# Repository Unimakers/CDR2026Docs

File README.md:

---
title: "README & MICRODOC"
layout: default
---
# Documentation de l'association UniMakers pour la CDR2026

Table de contenu:
- [Documentation de l'association UniMakers pour la CDR2026](#documentation-de-lassociation-unimakers-pour-la-cdr2026)
  - [Comment créer une page ?](#comment-créer-une-page-)
  - [Comment afficher un modèle 3D](#comment-afficher-un-modèle-3d)

## Comment créer une page ?

Allez dans le dossier correspondant au thème de la page, 

exemple pour l'élec du robot principal: Robot/Elec/

Créez un nouveau fichier pour votre nouvelle page.

Rajoutez en haut du fichier:

```yaml
---
title: "Titre de votre page"
layout: technical
---
```

Utilisez `layout: technical` si vous souhaitez utiliser les modèles 3D ou le visualiseur kicad dans votre page, sinon utilisez `layout: default` pour réduire le temps de chargement de la page en supprimant les imports inutiles.

Les clés de définition doivent se trouver entre les deux `---`.
Après le deuxième `---` vous pouvez écrire le contenu de la page **en markdown**.

Vous pouvez rajouter un 
```yaml
has_children: true
```
si vous souhaitez faire de cette page une page de catégorie qui aura donc des sous-pages.

Pour mettre cette page en tant que sous-page dans une catégorie (et non à la racine) vous devez rajouter une clé `parent` et eventuellement une clé `grand_parent`:

La clé `parent` permettra de définir le parent direct de la page, la valeur doit etre le titre de la page parent.

Exemple, si vous créez une page dans la catégorie `Electronique` du `Robot` vous devrez définir la clé `parent` avec la valeur `Electronique`.

La clé `grand_parent` permettra de définir le grand parent de la page, c'est à dire la catégorie racine, la valeur doit etre le titre du grand parent.

Exemple, si vous créez une page dans la catégorie `Electronique` du `Robot` vous devrez définir la clé `grand_parent` avec la valeur `Robot`

Actuellement l'arbre des titres et catégories est:
```
Racine:
|-Présentation
|-Robot:
| |-Mécanique
| |-Stratégie
|-Pami:
| |-Mécanique
| |-Stratégie
|-Electronique
|-Programmation
| |-Déplacement
| |-Détection
```

Exemple pour créer une catégorie `Actionneurs` dans `Mécanique` sous `Robot` et ensuite créer une page `Pince`:

On crée le dossier `Robot/Meca/Actionneurs` (c'est mieux pour la lisibilité de trier les pages dans des dossiers, techniquement on pourrait tout laisser à la racine).

On crée le fichier `Robot/Meca/Actionneurs/Actionneurs.md`:
```md
---
title: Actionneurs
parent: Mécanique
grand_parent: Robot
has_children: true
layout: default
---
# Les actionneurs de notre robot
Le robot a besoin d'actionneurs pour fonctionner
```

On crée le fichier `Robot/Meca/Actionneurs/Pince.md`:
```md
---
title: Pince
parent: Actionneurs
grand_parent: Mécanique
has_children: true
layout: default
---
# La pince du robot
La pince du robot, nécessaire pour attraper.....
```

## Comment afficher un modèle 3D

Assurez vous d'avoir défini `layout: technical` au lieu de `layout: default`.

Dans votre code markdown rajoutez:
```md
<model-viewer alt="Texte de déscription du modèle 3D" src="url / chemin du modèle 3D" ar shadow-intensity="1" camera-controls touch-action="pan-y"></model-viewer>

Ou

{%raw%}{{%include model3D.html alt="Texte de description du modèle 3D" model="url / chemin du modèle 3D"%}}{%endraw%}
``` 
Le modèle 3D **doit** être en format GLTF / GLB.

## Comment utiliser le visionneur KiCad

Assurez vous d'avoir défini `layout: technical` au lieu de `layout: default`.

- Si vous ne souhaitez que le schématique:

Dans votre code markdown rajoutez:
```md
<kicanvas-embed src="chemin/vers/fichier.kicad_sch" controls="basic"></kicanvas-embed>
```

- Si vous souhaitez le schématique ET la PCB;

Dans votre code markdown rajoutez:
```md
<kicanvas-embed controls="full">
<kicanvas-source src="chemin/vers/fichier.kicad_sch"></kicanvas-source>
<kicanvas-source src="chemin/vers/fichier.kicad_pcb"></kicanvas-source>
</kicanvas-embed>
```

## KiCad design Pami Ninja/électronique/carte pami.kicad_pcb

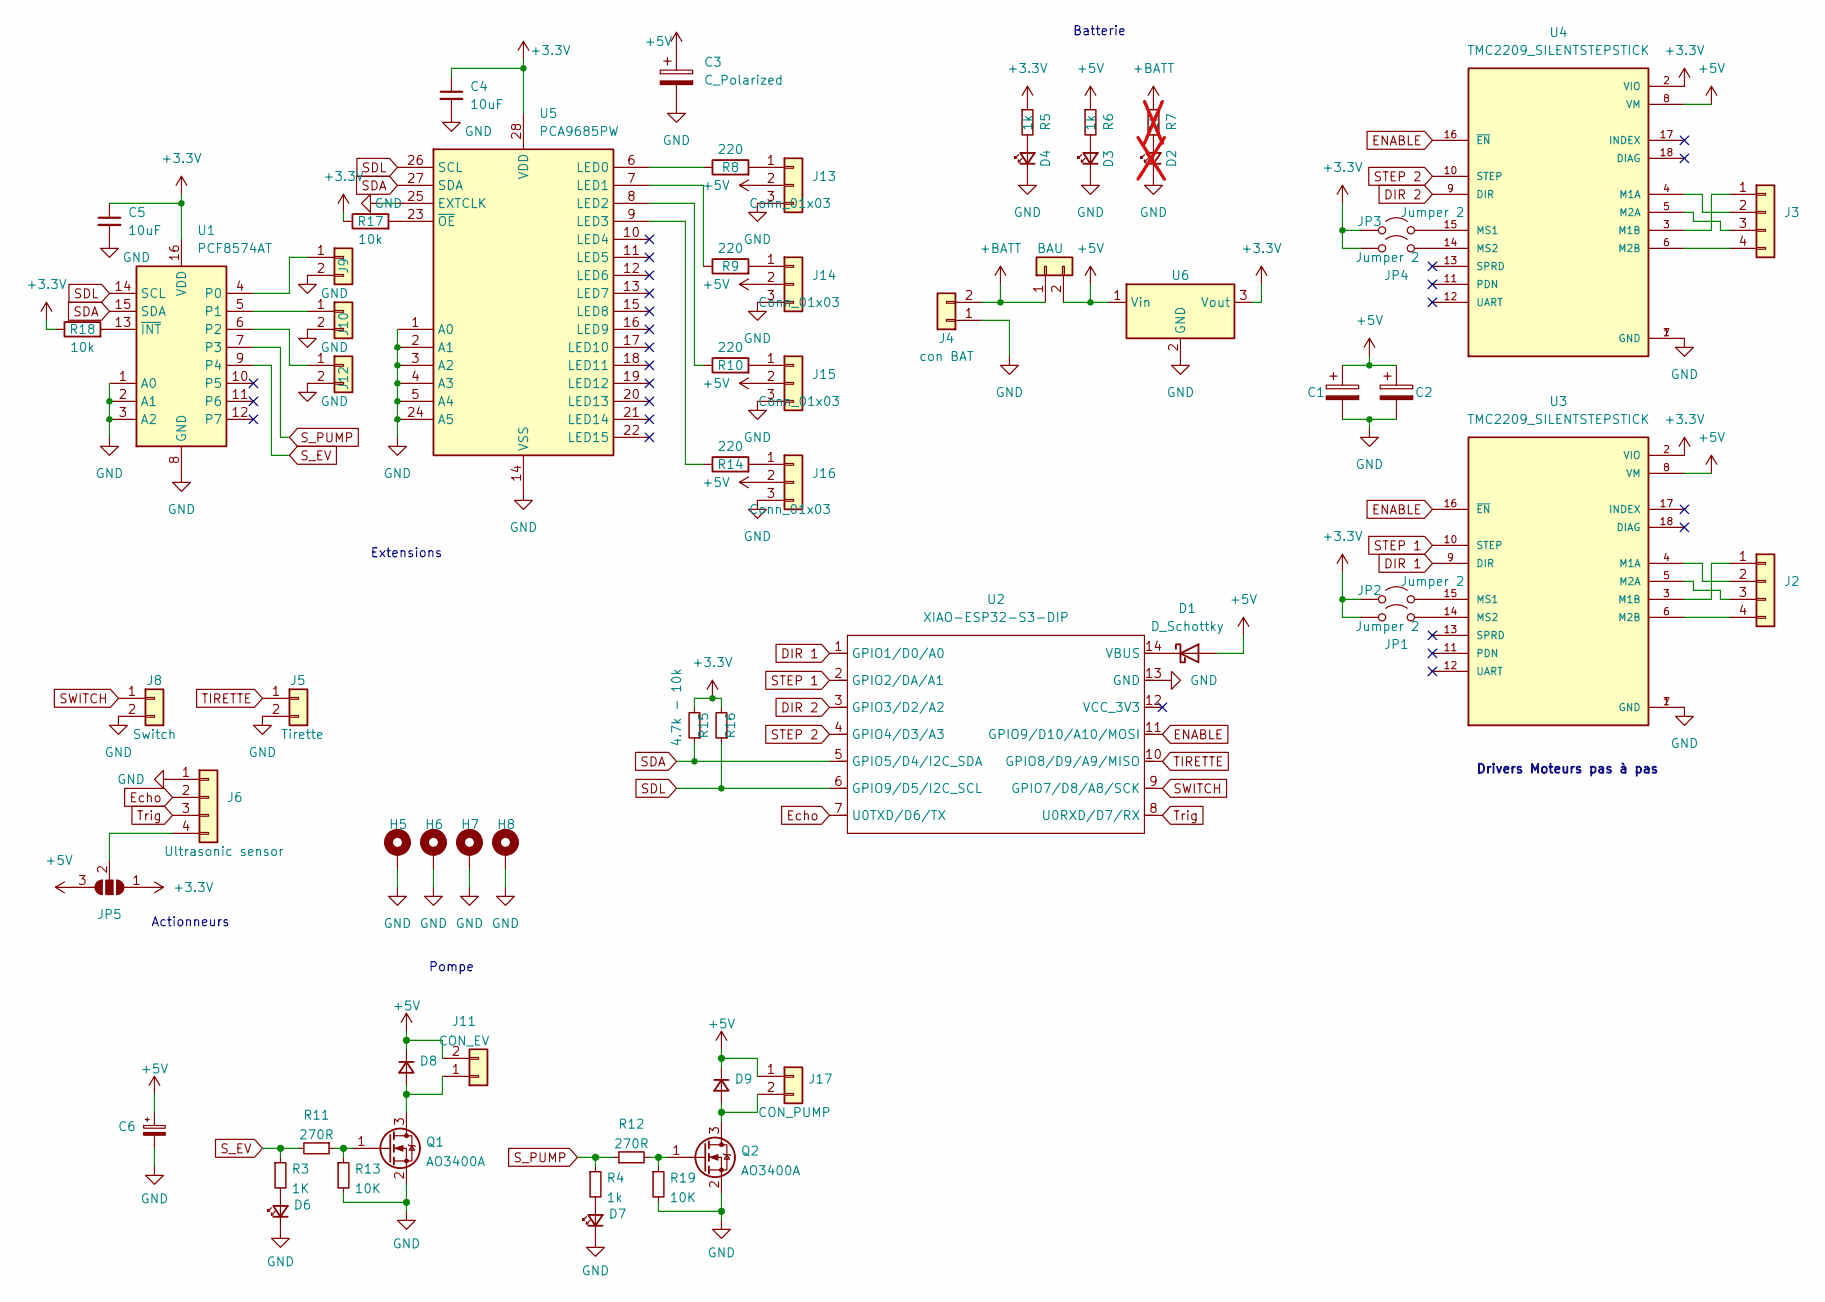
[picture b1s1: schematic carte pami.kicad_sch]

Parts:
C1, C2: C_Polarized; CP_Radial_D8.0mm_P3.80mm
C3: C_Polarized; CP_Radial_D8.0mm_P5.00mm
C4, C5: 10uF; C_1206_3216Metric_Pad1.33x1.80mm_HandSolder
C6: C_Polarized_Small; CP_Radial_D8.0mm_P5.00mm
D1: D_Schottky; D_DO-41_SOD81_P10.16mm_Horizontal
D2: LED_Small; LED_1206_3216Metric_Pad1.42x1.75mm_HandSolder; not fitted
D3, D4, D6, D7: LED_Small; LED_1206_3216Metric_Pad1.42x1.75mm_HandSolder
D8, D9: D_Small; D_SMA_Handsoldering
H5, H6, H7, H8: MountingHole_3.2mm_M3_Pad
J1: BAU; Molex_KK-254_AE-6410-02A_1x02_P2.54mm_Vertical
J2, J3: Conn_01x04; Molex_KK-254_AE-6410-04A_1x04_P2.54mm_Vertical
J4: con BAT; AMASS_XT60-F_1x02_P7.20mm_Vertical
J5: Tirette; Molex_KK-254_AE-6410-02A_1x02_P2.54mm_Vertical
J6: Ultrasonic sensor; Molex_KK-254_AE-6410-04A_1x04_P2.54mm_Vertical
J8: Switch; Molex_KK-254_AE-6410-02A_1x02_P2.54mm_Vertical
J9, J10, J12: Conn_01x02; Molex_KK-254_AE-6410-02A_1x02_P2.54mm_Vertical
J11: CON_EV; Molex_KK-254_AE-6410-02A_1x02_P2.54mm_Vertical
J13, J14, J15, J16: Conn_01x03; PinHeader_1x03_P2.54mm_Vertical
J17: CON_PUMP; Molex_KK-254_AE-6410-02A_1x02_P2.54mm_Vertical
JP1, JP2, JP3, JP4: Jumper 2; SolderJumper-2_P1.3mm_Open_RoundedPad1.0x1.5mm
JP5: SolderJumper_3_Open; SolderJumper-3_P1.3mm_Open_RoundedPad1.0x1.5mm_NumberLabels
Q1, Q2: AO3400A; SOT-23
R3: 1K; R_1206_3216Metric_Pad1.30x1.75mm_HandSolder
R4, R5, R6: 1k; R_1206_3216Metric_Pad1.30x1.75mm_HandSolder
R7: 1k; R_1206_3216Metric_Pad1.30x1.75mm_HandSolder; not fitted
R8, R9, R10, R14: 220; R_1206_3216Metric_Pad1.30x1.75mm_HandSolder
R11, R12: 270R; R_1206_3216Metric_Pad1.30x1.75mm_HandSolder
R13, R19: 10K; R_1206_3216Metric_Pad1.30x1.75mm_HandSolder
R15: 4.7k - 10k; R_1206_3216Metric_Pad1.30x1.75mm_HandSolder
R16: R_Small; R_1206_3216Metric_Pad1.30x1.75mm_HandSolder
R17, R18: 10k; R_1206_3216Metric_Pad1.30x1.75mm_HandSolder
U1: PCF8574AT; SOIC-16W_7.5x10.3mm_P1.27mm
U2: XIAO-ESP32-S3-DIP; XIAO-ESP32S3-DIP
U3, U4: TMC2209_SILENTSTEPSTICK; MODULE_TMC2209_SILENTSTEPSTICK; PARTREV 1.20
U5: PCA9685PW; TSSOP-28_4.4x9.7mm_P0.65mm
U6: TSR1-2433E; Converter_DCDC_TRACO_TSR1-xxxxE_THT

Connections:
+3.3V: C4.1, C5.1, JP1.1 (A), JP2.1 (A), JP3.1 (A), JP4.1 (A), JP5.1 (A), R5.1, R15.2, R16.2, R17.1, R18.1, U1.16 (VDD), U3.2 (VIO), U4.2 (VIO), U5.28 (VDD), U6.3 (Vout)
+5V: C1.1, C2.1, C3.1, C6.1, D1.2 (A), D8.1 (K), D9.1 (K), J1.2, J11.2, J13.2, J14.2, J15.2, J16.2, J17.1, JP5.3 (B), R6.1, U3.8 (VM), U4.8 (VM), U6.1 (Vin)
+BATT: J1.1, J4.2, R7.1
DIR 1: U2.1 (GPIO1/D0/A0), U3.9 (DIR)
DIR 2: U2.3 (GPIO3/D2/A2), U4.9 (DIR)
ENABLE: U2.11 (GPIO9/D10/A10/MOSI), U3.16 (~EN), U4.16 (~EN)
Echo: J6.2, U2.7 (U0TXD/D6/TX)
GND: C1.2, C2.2, C3.2, C4.2, C5.2, C6.2, D2.1 (K), D3.1 (K), D4.1 (K), D6.1 (K), D7.1 (K), H5.1, H6.1, H7.1, H8.1, J4.1, J5.2, J6.1, J8.2, J9.2, J10.2, J12.2, J13.3, J14.3, J15.3, J16.3, Q1.2 (S), Q2.2 (S), R13.2, R19.2, U1.1 (A0), U1.2 (A1), U1.3 (A2), U1.8 (GND), U2.13 (GND), U3.1 (GND), U3.7 (GND), U4.1 (GND), U4.7 (GND), U5.1 (A0), U5.2 (A1), U5.3 (A2), U5.4 (A3), U5.5 (A4), U5.14 (VSS), U5.24 (A5), U5.25 (EXTCLK), U6.2 (GND)
unnamed: D1.1 (K), U2.14 (VBUS)
unnamed: D2.2 (A), R7.2
unnamed: D3.2 (A), R6.2
unnamed: D4.2 (A), R5.2
unnamed: D6.2 (A), R3.2
unnamed: D7.2 (A), R4.2
unnamed: D8.2 (A), J11.1, Q1.3 (D)
unnamed: D9.2 (A), J17.2, Q2.3 (D)
unnamed: J2.1, U3.3 (M1B)
unnamed: J2.2, U3.4 (M1A)
unnamed: J2.3, U3.5 (M2A)
unnamed: J2.4, U3.6 (M2B)
unnamed: J3.1, U4.3 (M1B)
unnamed: J3.2, U4.4 (M1A)
unnamed: J3.3, U4.5 (M2A)
unnamed: J3.4, U4.6 (M2B)
unnamed: J6.4, JP5.2 (C)
unnamed: J9.1, U1.4 (P0)
unnamed: J10.1, U1.5 (P1)
unnamed: J12.1, U1.6 (P2)
unnamed: J13.1, R8.2
unnamed: J14.1, R9.2
unnamed: J15.1, R10.2
unnamed: J16.1, R14.2
unnamed: JP1.2 (B), U3.14 (MS2)
unnamed: JP2.2 (B), U3.15 (MS1)
unnamed: JP3.2 (B), U4.15 (MS1)
unnamed: JP4.2 (B), U4.14 (MS2)
unnamed: Q1.1 (G), R11.1, R13.1
unnamed: Q2.1 (G), R12.2, R19.1
unnamed: R18.2, U1.13 (~INT)
unnamed: R8.1, U5.6 (LED0)
unnamed: R9.1, U5.7 (LED1)
unnamed: R10.1, U5.8 (LED2)
unnamed: R14.1, U5.9 (LED3)
unnamed: R17.2, U5.23 (~OE)
SDA: R15.1, U1.15 (SDA), U2.5 (GPIO5/D4/I2C_SDA), U5.27 (SDA)
SDL: R16.1, U1.14 (SCL), U2.6 (GPIO9/D5/I2C_SCL), U5.26 (SCL)
STEP 1: U2.2 (GPIO2/DA/A1), U3.10 (STEP)
STEP 2: U2.4 (GPIO4/D3/A3), U4.10 (STEP)
SWITCH: J8.1, U2.9 (GPIO7/D8/A8/SCK)
S_EV: R3.1, R11.2, U1.9 (P4)
S_PUMP: R4.1, R12.1, U1.7 (P3)
TIRETTE: J5.1, U2.10 (GPIO8/D9/A9/MISO)
Trig: J6.3, U2.8 (U0RXD/D7/RX)

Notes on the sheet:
Batterie
Pompe
Actionneurs
Drivers Moteurs pas à pas
Extensions

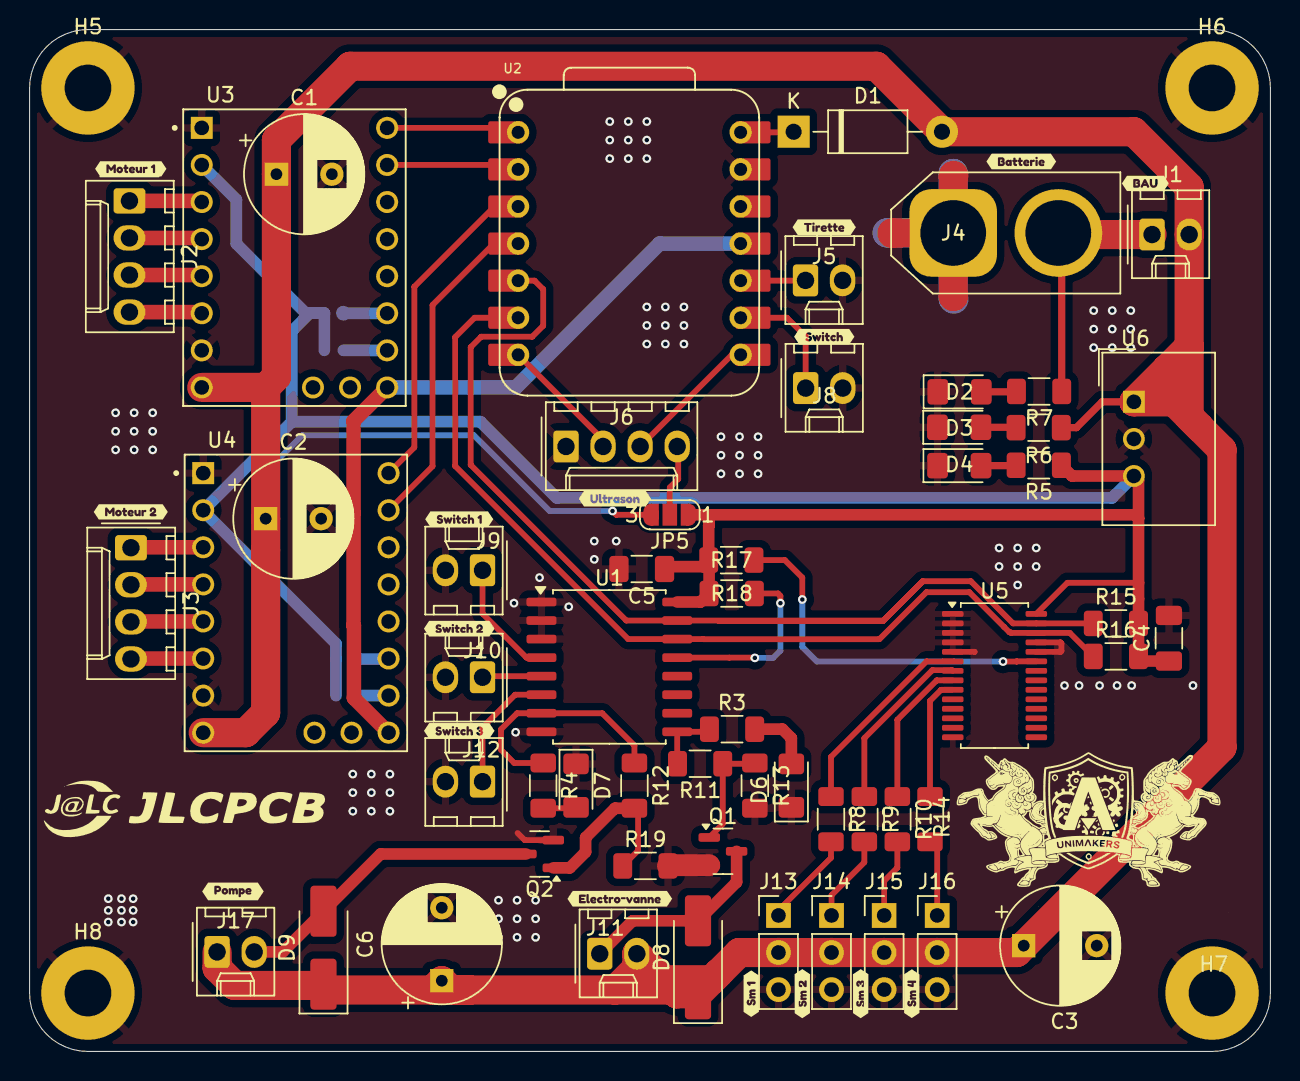
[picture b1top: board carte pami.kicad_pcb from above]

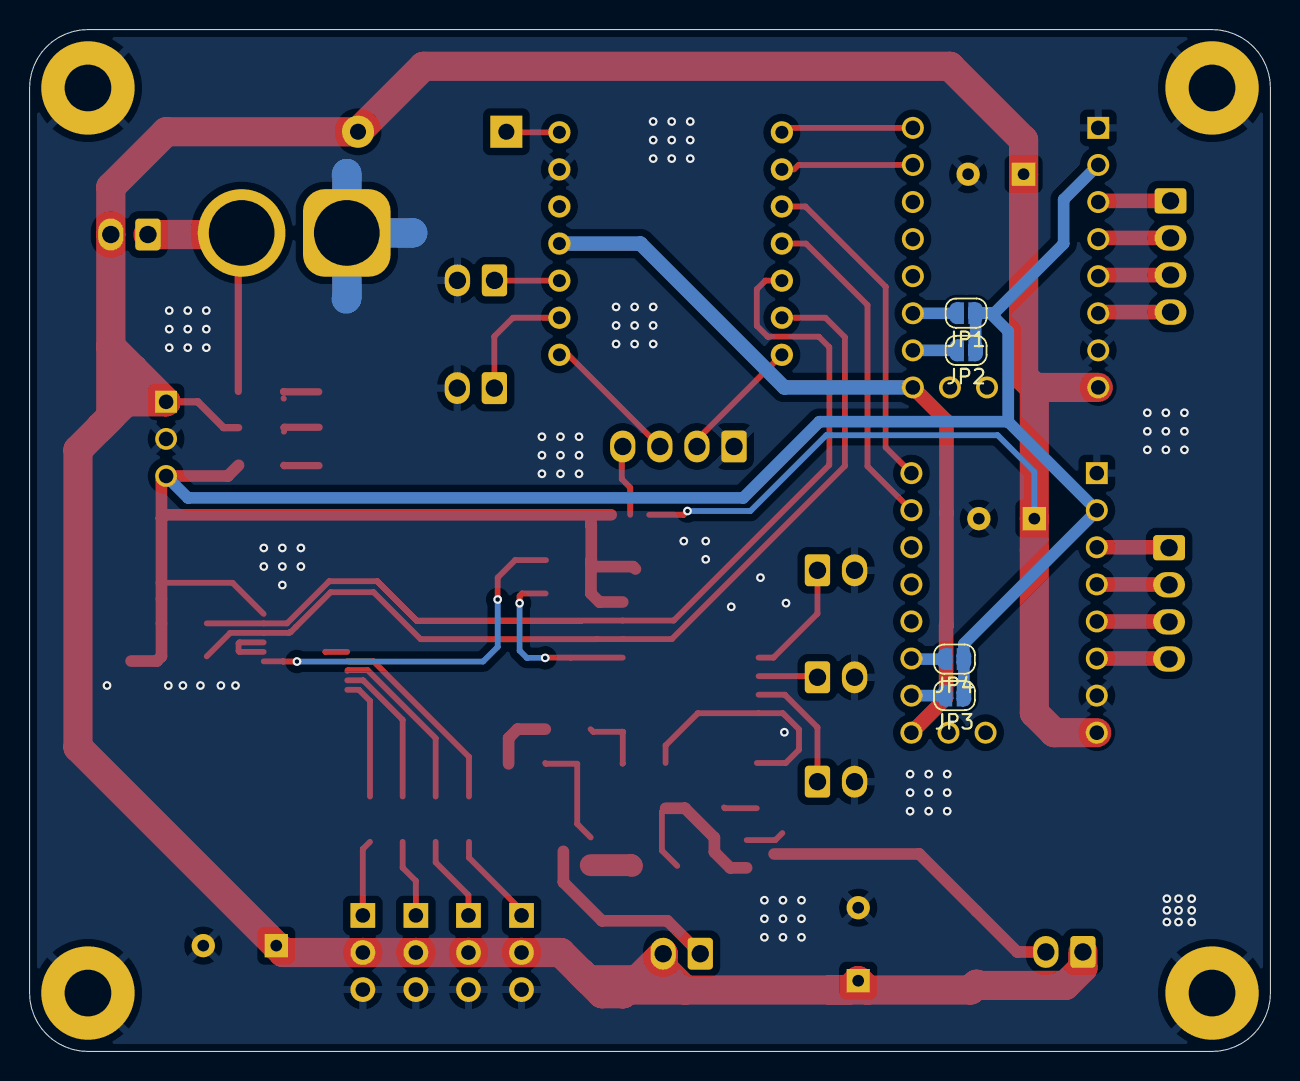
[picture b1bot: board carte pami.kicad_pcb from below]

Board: 2 copper layers, 85.0 x 70.0 mm, 80 parts (4 on the bottom side), 53 nets.

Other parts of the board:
kibuzzard-69BD4C51: G***; kibuzzard-69BD4C51
kibuzzard-69BD4C98: G***; kibuzzard-69BD4C98
kibuzzard-69BD4CAE: G***; kibuzzard-69BD4CAE
kibuzzard-69BD4CC4: G***; kibuzzard-69BD4CC4
kibuzzard-69BD4CEF: G***; kibuzzard-69BD4CEF
kibuzzard-69BD4D3C: G***; kibuzzard-69BD4D3C
kibuzzard-69BD4D5C: G***; kibuzzard-69BD4D5C
kibuzzard-69BD4D83: G***; kibuzzard-69BD4D83
kibuzzard-69BD4D93: G***; kibuzzard-69BD4D93
kibuzzard-69BD4EA4: G***; kibuzzard-69BD4EA4
kibuzzard-69BD4EB4: G***; kibuzzard-69BD4EB4
kibuzzard-69BD4EFE: G***; kibuzzard-69BD4EFE
kibuzzard-69BD4FA7: G***; kibuzzard-69BD4FA7
kibuzzard-69BD4FC7: G***; kibuzzard-69BD4FC7
kibuzzard-69BD4FD6: G***; kibuzzard-69BD4FD6
kibuzzard-69BD4FE1: G***; kibuzzard-69BD4FE1

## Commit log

2025-11-28 init of CDR2026 Docs
2025-11-28 some changes
2026-01-01 Bump just-the-docs from 0.10.1 to 0.10.2
    Bumps [just-the-docs](https://github.com/just-the-docs/just-the-docs) from 0.10.1 to 0.10.2.
    - [Release notes](https://github.com/just-the-docs/just-the-docs/releases)
    - [Changelog](https://github.com/just-the-docs/just-the-docs/blob/main/CHANGELOG.md)
    - [Commits](https://github.com/just-the-docs/just-the-docs/compare/v0.10.1...v0.10.2)
    ---
    updated-dependencies:
2026-01-02 Bump just-the-docs from 0.10.1 to 0.11.0
    Bumps [just-the-docs](https://github.com/just-the-docs/just-the-docs) from 0.10.1 to 0.11.0.
    - [Release notes](https://github.com/just-the-docs/just-the-docs/releases)
    - [Changelog](https://github.com/just-the-docs/just-the-docs/blob/main/CHANGELOG.md)
    - [Commits](https://github.com/just-the-docs/just-the-docs/compare/v0.10.1...v0.11.0)
    ---
    updated-dependencies:
2026-01-16 first commit doc elec
2026-01-19 intro
2026-01-20 test model 3d
2026-01-20 add kicanvas
2026-01-20 test 2
2026-01-20 test pcb
2026-01-20 add lfs
2026-01-20 partie 2
2026-01-20 remove lfs
2026-01-20 Bump just-the-docs from 0.10.1 to 0.11.1
    Bumps [just-the-docs](https://github.com/just-the-docs/just-the-docs) from 0.10.1 to 0.11.1.
    - [Release notes](https://github.com/just-the-docs/just-the-docs/releases)
    - [Changelog](https://github.com/just-the-docs/just-the-docs/blob/main/CHANGELOG.md)
    - [Commits](https://github.com/just-the-docs/just-the-docs/compare/v0.10.1...v0.11.1)
    ---
    updated-dependencies:
2026-01-20 script url
2026-01-20 Disable LFS in GitHub Pages workflow
2026-01-20 Update GitHub Actions workflow for LFS support
    Added steps to handle Git LFS authentication and checkout.
2026-01-20 avancée partie elec
2026-01-21 avancement
2026-01-21 création pami ninja
2026-01-21 sous page pami ninja
2026-01-21 actionneurs base roulante ficher créer
2026-01-21 avancée conception
2026-01-21 base roulante pami ninja
2026-01-21 début edit de la presentation de la coupe
2026-01-25 test + fix
2026-01-25 on teste
2026-01-26 test réglage problème navigation
2026-01-26 aaaaa
2026-01-26 test modif navig
2026-01-26 changement nav order
2026-01-26 aaaaaaaaaaaaaaaaaaaaaaaaaa
2026-01-26 pami ninja validation.md
2026-01-26 pami ninja
2026-01-26 pami
2026-01-26 pami supprimé
2026-01-26 modif
2026-01-26 test
2026-01-26 on test encore
2026-01-26 azdhaefhfaeo
2026-01-26 ajoiausbha
2026-01-26 Bump just-the-docs from 0.10.1 to 0.12.0
    Bumps [just-the-docs](https://github.com/just-the-docs/just-the-docs) from 0.10.1 to 0.12.0.
    - [Release notes](https://github.com/just-the-docs/just-the-docs/releases)
    - [Changelog](https://github.com/just-the-docs/just-the-docs/blob/main/CHANGELOG.md)
    - [Commits](https://github.com/just-the-docs/just-the-docs/compare/v0.10.1...v0.12.0)
    ---
    updated-dependencies:
2026-01-30 ajout actionneurs et modifs autres
2026-01-30 actionneurs
2026-02-25 aaaaaa
2026-02-25 aaaaaaaa
2026-02-25 aaaaaaaaaaaaaaaaa
2026-03-11 aaaa
2026-04-20 Create schématique
2026-04-20 update txt et syst pneumatique
    Updated the actuator section with additional details on the mechanical architecture and pneumatic system. Improved clarity and added information on the design choices and functionality.
2026-04-20 mots en gras
2026-04-20 modif lettre
2026-04-20 points
2026-05-26 prog pami ninja
2026-05-26 idaj
2026-05-26 élec ninja
2026-05-27 assemblage pami ninja
2026-05-27 lhjl
2026-05-27 ajout pcb et schématique
2026-05-27 adizaugidzau
2026-05-29 modif texte
